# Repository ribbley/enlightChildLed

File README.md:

# enlightChildLed
Small gadget for kids to play with and learn additive color mixing.

# TODOs:
- add pcb design files (KiCAD)
- document process (design, component search, ordering, assembly, firmware-developing, testing)
- add real photos

# Contact me, if you want to learn more about this project!

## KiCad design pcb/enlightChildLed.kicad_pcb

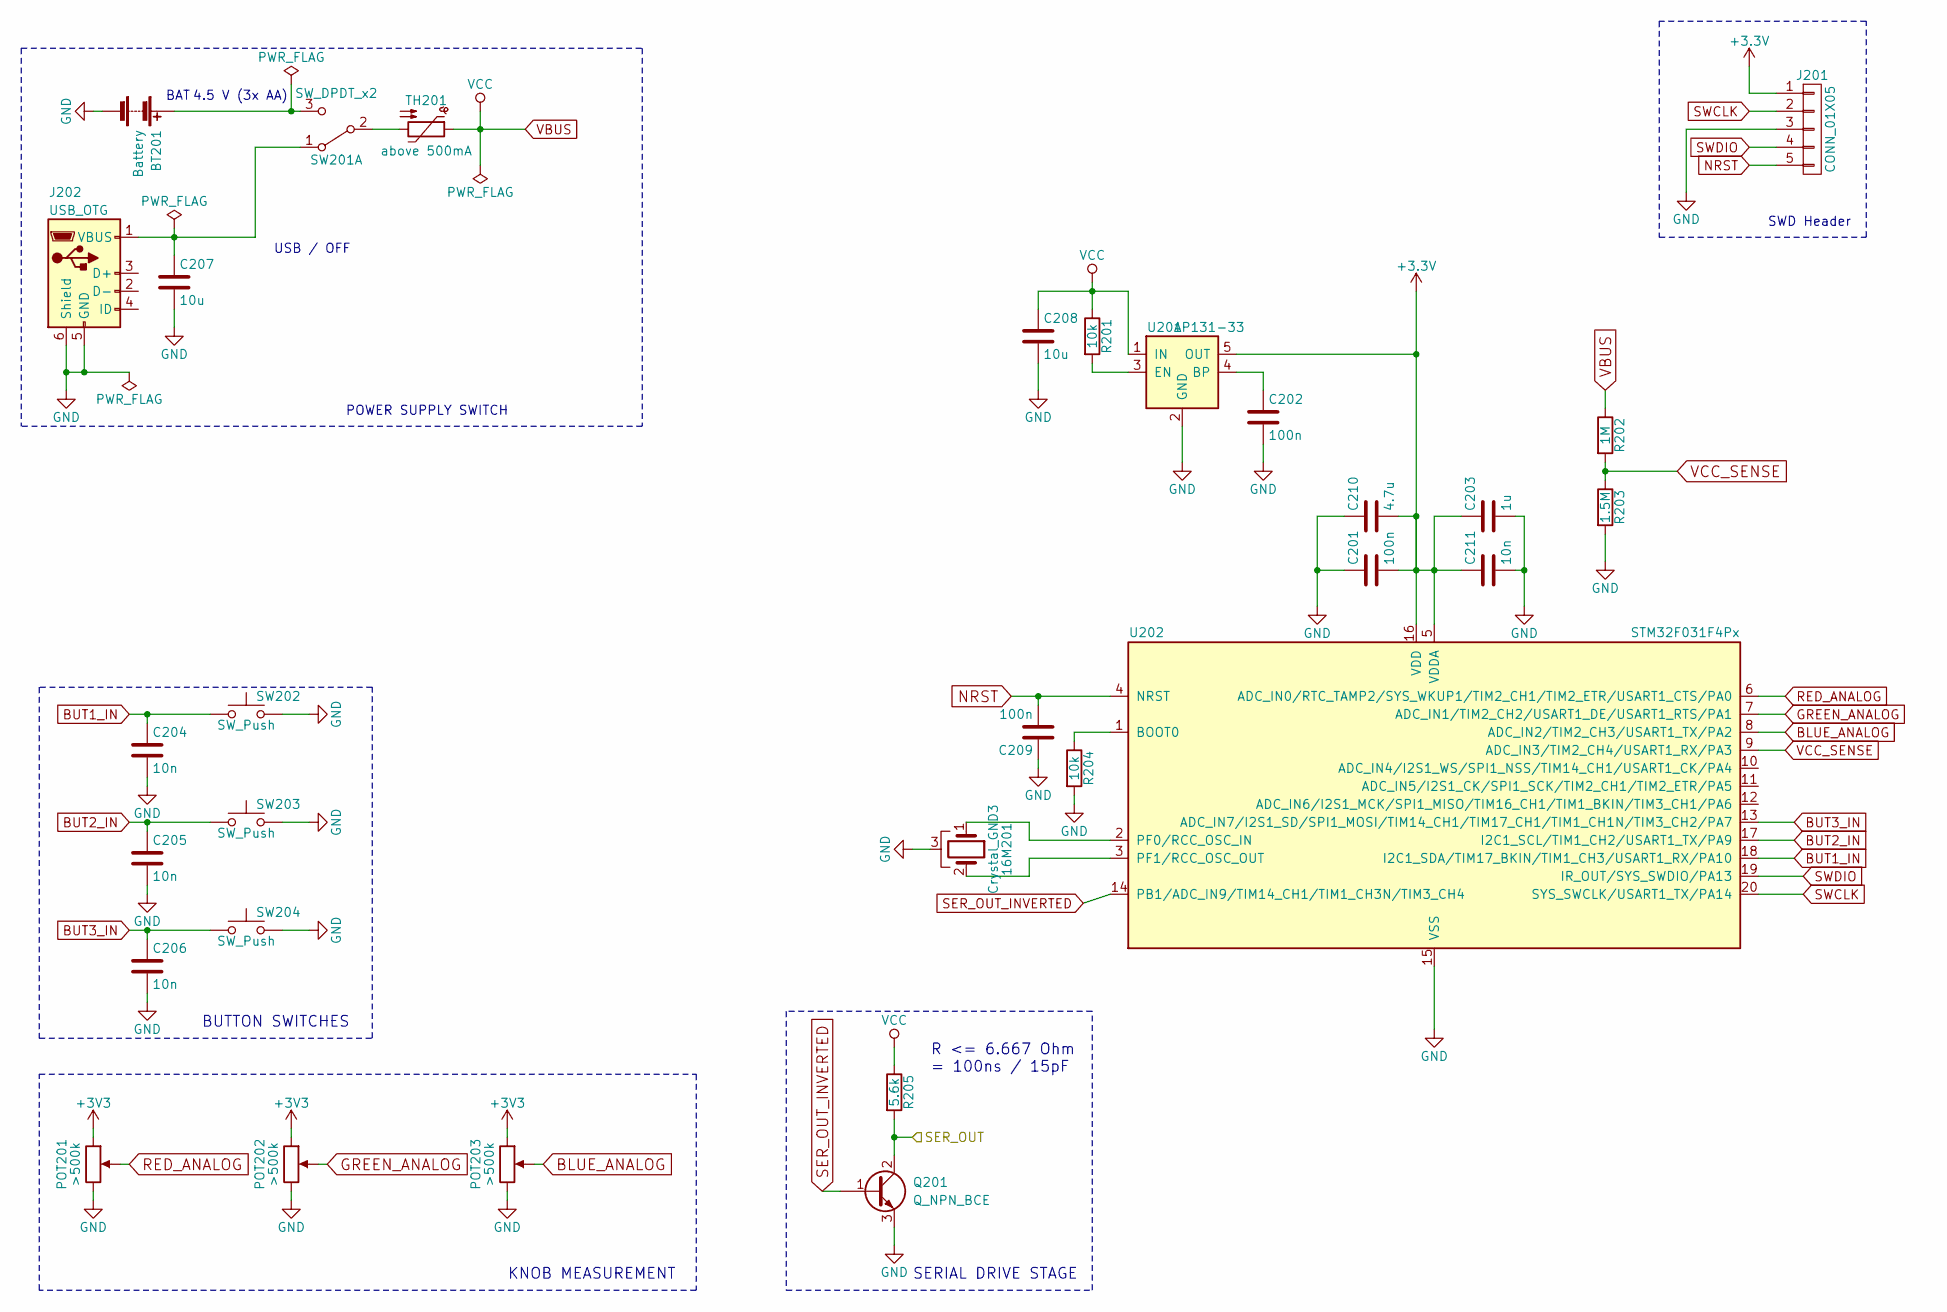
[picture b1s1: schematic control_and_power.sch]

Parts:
16M201: Crystal_GND3; Resonator_SMD_muRata_SFSKA-3pin_7.9x3.8mm
BT201: Battery; Keystone_2479_3xAAA
C201, C202, C209: 100n; C_0603
C203: 1u; C_0603
C204, C205, C206, C211: 10n; C_0603
C207, C208: 10u; C_0603
C210: 4.7u; C_0603
J201: CONN_01X05; Wafer_Vertical15x5.8x7RM2.5-5
J202: USB_OTG; USB_Mini-B
POT201, POT202, POT203: >500k; Potentiometer_Bourns_PTV09A-1_Horizontal
Q201: Q_NPN_BCE; SOT-23
R201, R204: 10k; R_0603
R202: 1M; R_0603
R203: 1.5M; R_0603
R205: 5.6k; R_0603
SW201: SW_DPDT_x2; SW_SPDT_PCM12
SW202, SW203, SW204: SW_Push; SW_PUSH_6mm
TH201: above 500mA; R_0402
U201: AP131-33; SOT-23-5
U202: STM32F031F4Px; TSSOP-20_4.4x6.5mm_Pitch0.65mm

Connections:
/LED Matrix/SER_INPUT: Q201.2 (C), R205.2; also elsewhere on the board
BLUE_ANALOG: POT203.2, U202.8 (ADC_IN2/TIM2_CH3/USART1_TX/PA2)
BUT1_IN: C204.1, SW202.1, U202.18 (I2C1_SDA/TIM17_BKIN/TIM1_CH3/USART1_RX/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)
BUT2_IN: C205.1, SW203.1, U202.17 (I2C1_SCL/TIM1_CH2/USART1_TX/PA9)
BUT3_IN: C206.1, SW204.1, U202.13 (ADC_IN7/I2S1_SD/SPI1_MOSI/TIM14_CH1/TIM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)
GND: 16M201.3, BT201.2 (-), C201.1, C202.2, C203.2, C204.2, C205.2, C206.2, C207.2, C208.2, C209.1, C210.1, C211.2, J201.3, J202.5 (GND), J202.6 (Shield), POT201.3, POT202.3, POT203.3, Q201.3 (E), R203.2, R204.2, SW202.2, SW203.2, SW204.2, U201.2 (GND), U202.15 (VSS); also elsewhere on the board
GREEN_ANALOG: POT202.2, U202.7 (ADC_IN1/TIM2_CH2/USART1_DE/USART1_RTS/P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)
NRST: C209.2, J201.5, U202.4 (NRST)
unnamed: 16M201.1, U202.2 (PF0/RCC_OSC_IN)
unnamed: 16M201.2, U202.3 (PF1/RCC_OSC_OUT)
unnamed: BT201.1 (+), SW201.3 (C)
unnamed: C202.1, U201.4 (BP)
unnamed: C207.1, J202.1 (VBUS), SW201.1 (A)
unnamed: R201.2, U201.3 (EN)
unnamed: R204.1, U202.1 (BOOT0)
unnamed: SW201.2 (B), TH201.2
RED_ANALOG: POT201.2, U202.6 (ADC_IN0/RTC_TAMP2/SYS_WKUP1/TIM2_CH1/TI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)
SER_OUT_INVERTED: Q201.1 (B), U202.14 (PB1/ADC_IN9/TIM14_CH1/TIM1_CH3N/TIM3_CH4)
SWCLK: J201.2, U202.20 (SYS_SWCLK/USART1_TX/PA14)
SWDIO: J201.4, U202.19 (IR_OUT/SYS_SWDIO/PA13)
VBUS: C208.1, R201.1, R202.1, R205.1, TH201.1, U201.1 (IN); also elsewhere on the board
VCC_SENSE: R202.2, R203.1, U202.9 (ADC_IN3/TIM2_CH4/USART1_RX/PA3)

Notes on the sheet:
SWD Header
USB / OFF
BAT
POWER SUPPLY SWITCH
4.5 V (3x AA)
KNOB MEASUREMENT
R <= 6.667 Ohm = 100ns / 15pF
SERIAL DRIVE STAGE
BUTTON SWITCHES

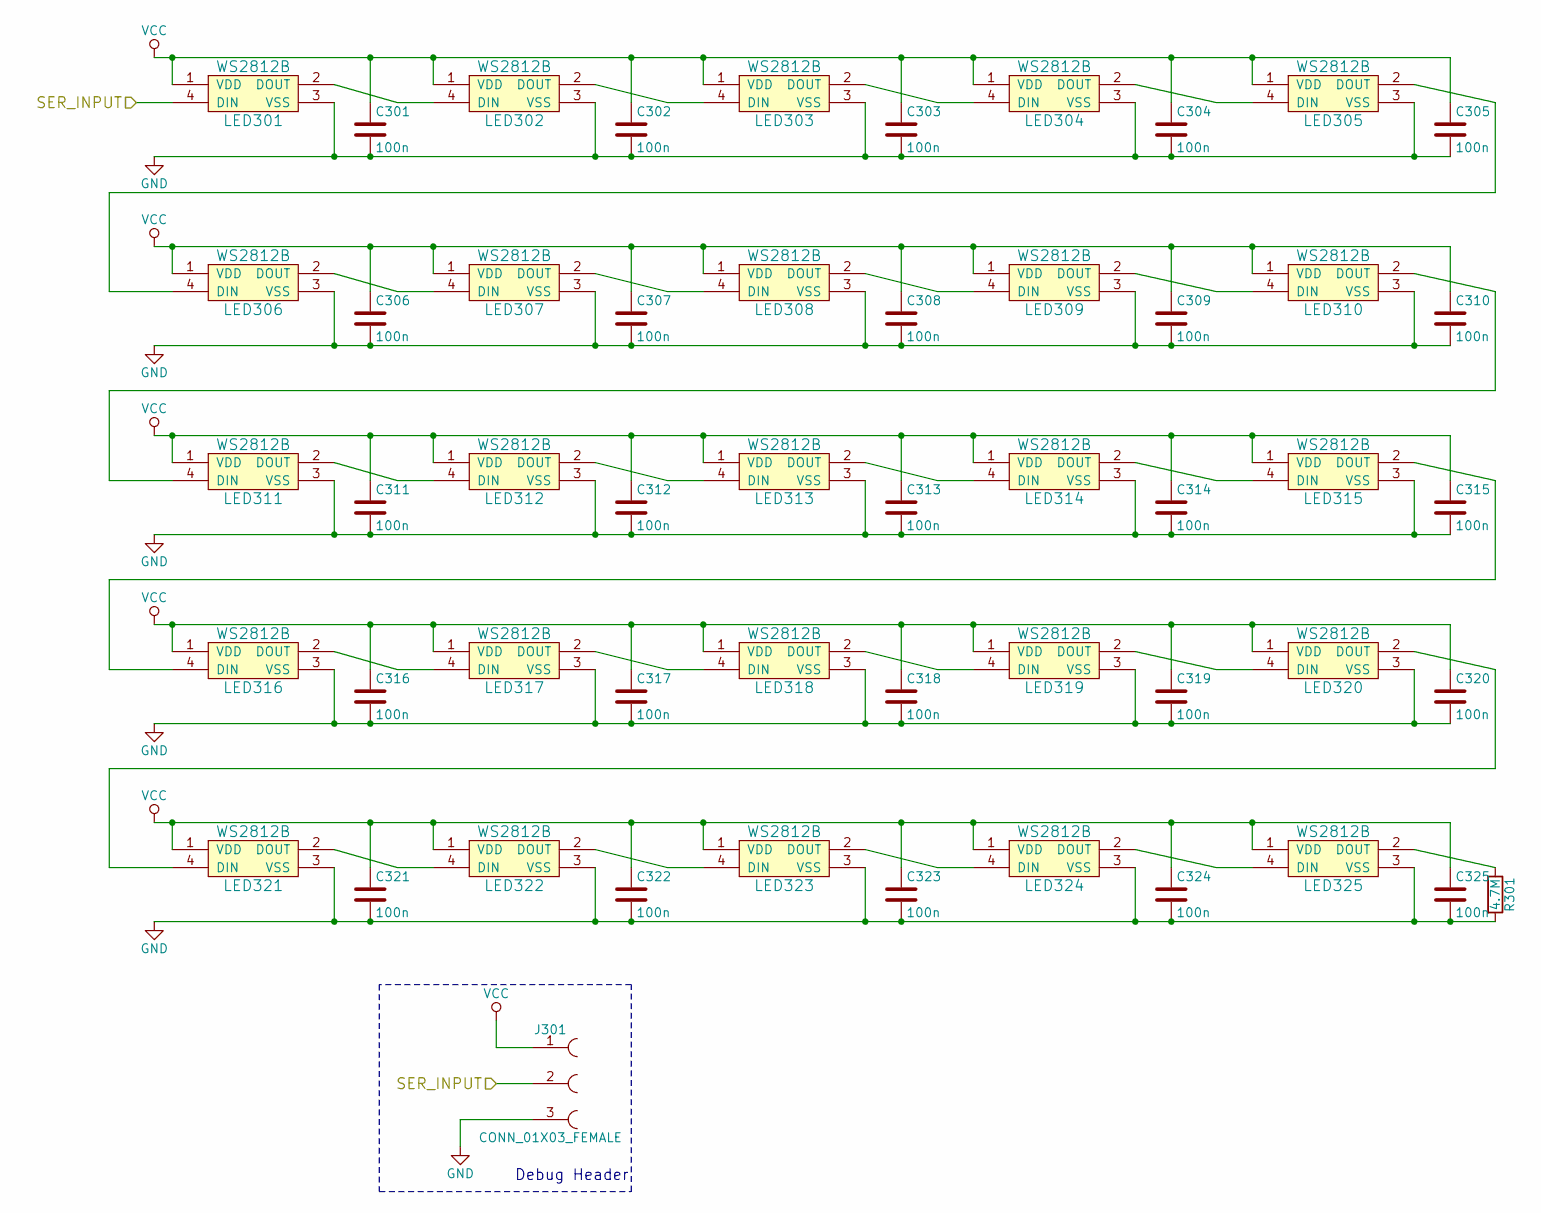
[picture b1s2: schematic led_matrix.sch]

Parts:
C301, C302, C303, C304, C305, C306, C307, C308, C309, C310, C311, C312, C313, C314, C315, C316, C317, C318, C319, C320, C321, C322, C323, C324, C325: 100n; C_0603
J301: CONN_01X03_FEMALE; PINHEAD1-3
LED301, LED302, LED303, LED304, LED305, LED306, LED307, LED308, LED309, LED310, LED311, LED312, LED313, LED314, LED315, LED316, LED317, LED318, LED319, LED320, LED321, LED322, LED323, LED324, LED325: WS2812B; LED_WS2812B-PLCC4
R301: 4.7M; R_0603

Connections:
/LED Matrix/SER_INPUT: J301.2, LED301.4 (DIN); also elsewhere on the board
GND: C301.2, C302.2, C303.2, C304.2, C305.2, C306.2, C307.2, C308.2, C309.2, C310.2, C311.2, C312.2, C313.2, C314.2, C315.2, C316.2, C317.2, C318.2, C319.2, C320.2, C321.2, C322.2, C323.2, C324.2, C325.2, J301.3, LED301.3 (VSS), LED302.3 (VSS), LED303.3 (VSS), LED304.3 (VSS), LED305.3 (VSS), LED306.3 (VSS), LED307.3 (VSS), LED308.3 (VSS), LED309.3 (VSS), LED310.3 (VSS), LED311.3 (VSS), LED312.3 (VSS), LED313.3 (VSS), LED314.3 (VSS), LED315.3 (VSS), LED316.3 (VSS), LED317.3 (VSS), LED318.3 (VSS), LED319.3 (VSS), LED320.3 (VSS), LED321.3 (VSS), LED322.3 (VSS), LED323.3 (VSS), LED324.3 (VSS), LED325.3 (VSS), R301.2; also elsewhere on the board
unnamed: LED301.2 (DOUT), LED302.4 (DIN)
unnamed: LED302.2 (DOUT), LED303.4 (DIN)
unnamed: LED303.2 (DOUT), LED304.4 (DIN)
unnamed: LED304.2 (DOUT), LED305.4 (DIN)
unnamed: LED305.2 (DOUT), LED306.4 (DIN)
unnamed: LED306.2 (DOUT), LED307.4 (DIN)
unnamed: LED307.2 (DOUT), LED308.4 (DIN)
unnamed: LED308.2 (DOUT), LED309.4 (DIN)
unnamed: LED309.2 (DOUT), LED310.4 (DIN)
unnamed: LED310.2 (DOUT), LED311.4 (DIN)
unnamed: LED311.2 (DOUT), LED312.4 (DIN)
unnamed: LED312.2 (DOUT), LED313.4 (DIN)
unnamed: LED313.2 (DOUT), LED314.4 (DIN)
unnamed: LED314.2 (DOUT), LED315.4 (DIN)
unnamed: LED315.2 (DOUT), LED316.4 (DIN)
unnamed: LED316.2 (DOUT), LED317.4 (DIN)
unnamed: LED317.2 (DOUT), LED318.4 (DIN)
unnamed: LED318.2 (DOUT), LED319.4 (DIN)
unnamed: LED319.2 (DOUT), LED320.4 (DIN)
unnamed: LED320.2 (DOUT), LED321.4 (DIN)
unnamed: LED321.2 (DOUT), LED322.4 (DIN)
unnamed: LED322.2 (DOUT), LED323.4 (DIN)
unnamed: LED323.2 (DOUT), LED324.4 (DIN)
unnamed: LED324.2 (DOUT), LED325.4 (DIN)
unnamed: LED325.2 (DOUT), R301.1
VBUS: C301.1, C302.1, C303.1, C304.1, C305.1, C306.1, C307.1, C308.1, C309.1, C310.1, C311.1, C312.1, C313.1, C314.1, C315.1, C316.1, C317.1, C318.1, C319.1, C320.1, C321.1, C322.1, C323.1, C324.1, C325.1, J301.1, LED301.1 (VDD), LED302.1 (VDD), LED303.1 (VDD), LED304.1 (VDD), LED305.1 (VDD), LED306.1 (VDD), LED307.1 (VDD), LED308.1 (VDD), LED309.1 (VDD), LED310.1 (VDD), LED311.1 (VDD), LED312.1 (VDD), LED313.1 (VDD), LED314.1 (VDD), LED315.1 (VDD), LED316.1 (VDD), LED317.1 (VDD), LED318.1 (VDD), LED319.1 (VDD), LED320.1 (VDD), LED321.1 (VDD), LED322.1 (VDD), LED323.1 (VDD), LED324.1 (VDD), LED325.1 (VDD); also elsewhere on the board

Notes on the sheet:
Debug Header

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
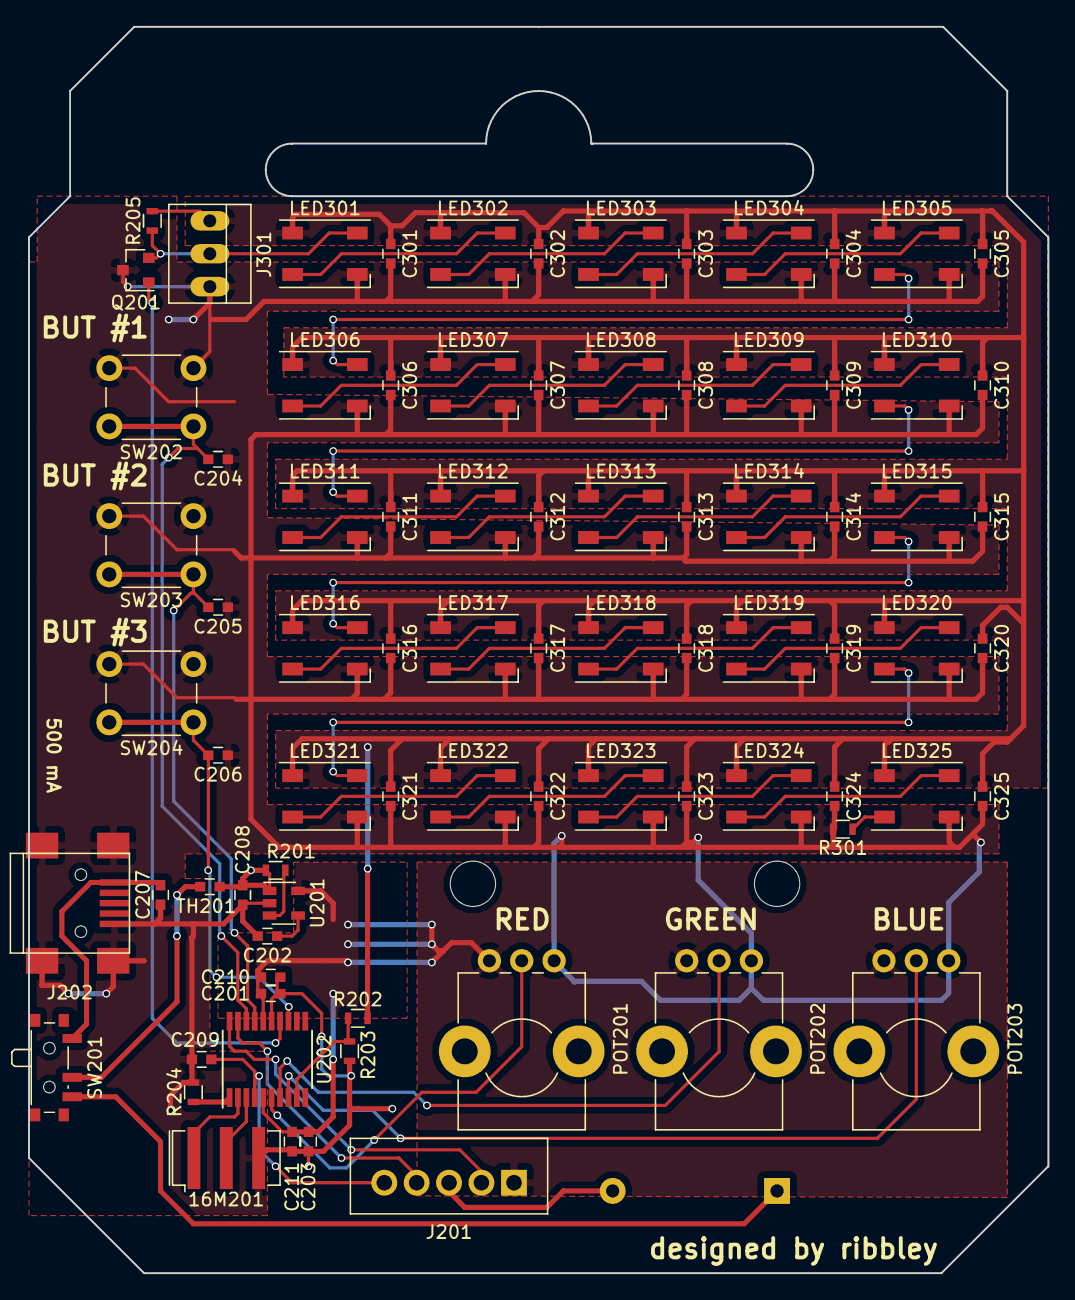
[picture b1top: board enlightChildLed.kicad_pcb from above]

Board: 2 copper layers, 78.7 x 96.3 mm, 83 parts (1 on the bottom side), 48 nets.

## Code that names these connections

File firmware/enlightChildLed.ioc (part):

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Mcu.Name=STM32F030F4Px
Mcu.Package=TSSOP20
Mcu.UserName=STM32F030F4Px
PA0.GPIOParameters=GPIO_Label
PA0.GPIO_Label=RED_ANALOG
PA0.Mode=IN0
PA0.Signal=ADC_IN0
PA1.GPIOParameters=GPIO_Label
PA1.GPIO_Label=GREEN_ANALOG
PA1.Mode=IN1
PA1.Signal=ADC_IN1
PA10.GPIOParameters=GPIO_PuPd,GPIO_Label
PA10.GPIO_Label=BUT1_IN
PA10.GPIO_PuPd=GPIO_PULLUP
PA10.Signal=GPIO_Input
PA13.Mode=Serial_Wire
PA13.Signal=SYS_SWDIO
PA14.Mode=Serial_Wire
PA14.Signal=SYS_SWCLK
PA2.GPIOParameters=GPIO_Label
PA2.GPIO_Label=BLUE_ANALOG
PA2.Mode=IN2
PA2.Signal=ADC_IN2
PA3.GPIOParameters=GPIO_Label
PA3.GPIO_Label=VCC_SENSE
PA3.Mode=IN3
PA3.Signal=ADC_IN3
PA5.Mode=TX_Only_Simplex_Unidirect_Master
PA5.Signal=SPI1_SCK
PA7.Mode=TX_Only_Simplex_Unidirect_Master
PA7.Signal=SPI1_MOSI
PA9.GPIOParameters=GPIO_PuPd,GPIO_Label
PA9.GPIO_Label=BUT2_IN
PA9.GPIO_PuPd=GPIO_PULLUP
PA9.Signal=GPIO_Input
PF0-OSC_IN.Mode=HSE-External-Oscillator
PF0-OSC_IN.Signal=RCC_OSC_IN
PF1-OSC_OUT.Mode=HSE-External-Oscillator
PF1-OSC_OUT.Signal=RCC_OSC_OUT
RCC.SYSCLKFreq_VALUE=40000000
RCC.SYSCLKSource=RCC_SYSCLKSOURCE_PLLCLK
board=enlightChildLed

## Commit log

2018-01-14 first commit, pcb design pending
2018-01-21 added pcb files from main pc
2018-01-22 Create LICENSE.md
    MIT license added
2018-01-22 first component order executed
2018-02-14 setting up toolchain
2018-02-14 added flash command
2018-02-21 switched to stm32f030f4p6
2018-02-24 cleaning repo
2018-02-24 debug config for atom plugin 'dbg-gdb-custom-server'
2018-03-19 progressing writing firmware, hardware working so far
2018-03-20 some led controlling functions
2018-04-08 some testing with assembler gpio banging
2018-04-08 not working state, but LL DMA progress
2018-04-09 low level driver dma initialization?
2018-04-17 not really working via dma, some clock/timing/interrupt issues
2018-04-24 much work, no use :(
2018-06-04 Rewriting firmware to use SPI, need to rewire -cut connection / put into HIGH-Z Mode PB1 -connect NPN transistor base to PA7 (old button3)
2018-06-30 added real pcb photos
2018-07-19 some reconfiguration
2018-08-27 primitive working version, only two buttons, has a buggy behavior at start
2019-02-27 starting 2nd pcb version, to fix old issues; hopefully release capable!
2019-03-01 progressing redrawing schematic
